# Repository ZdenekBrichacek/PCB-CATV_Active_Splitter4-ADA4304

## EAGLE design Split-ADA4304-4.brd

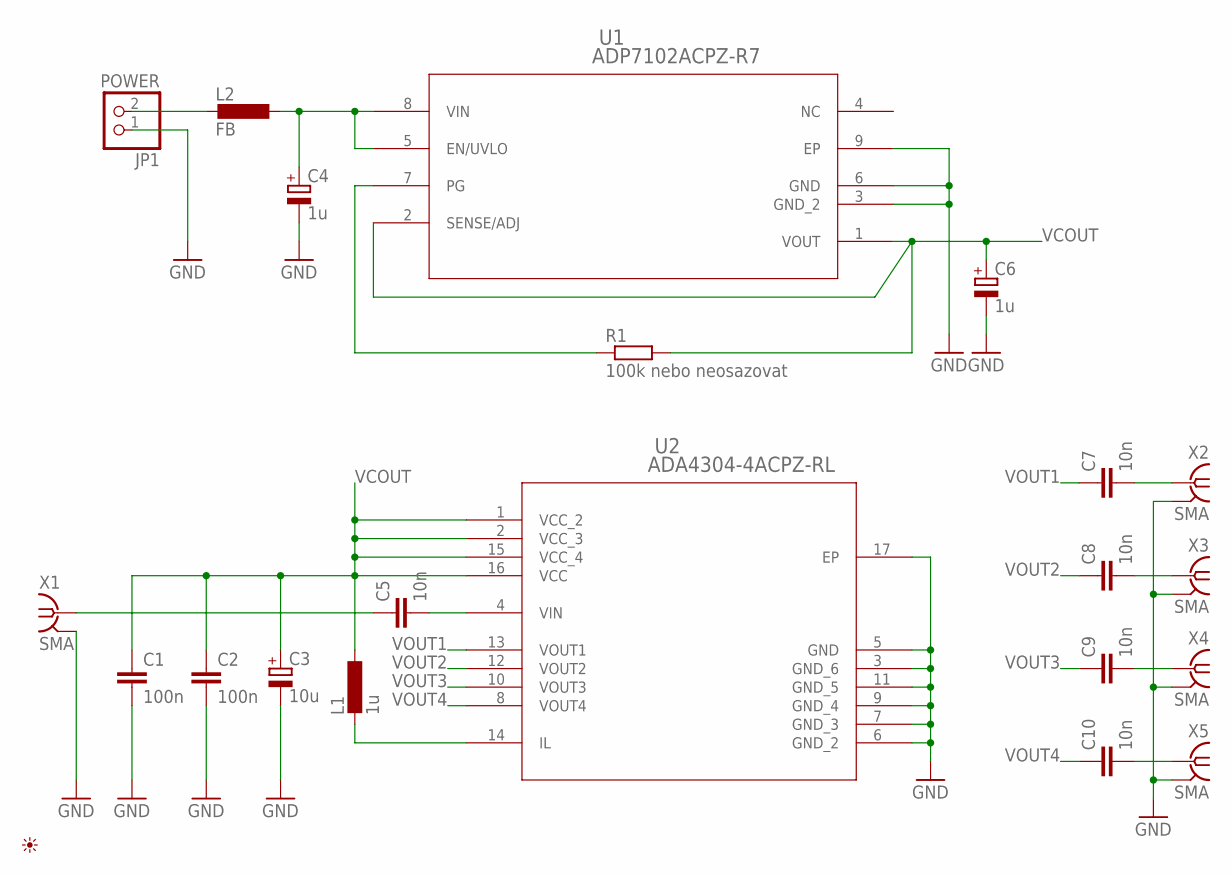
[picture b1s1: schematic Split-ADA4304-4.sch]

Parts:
C1, C2: 100n; C0603
C3: 10u; SMC_A
C4, C6: 1u; SMC_A
C5, C7, C8, C9, C10: 10n; C0603
JP1: POWER; 1X02
L1: 1u; L2012C
L2: FB; L2012C
PICTO1: PICTO_1
R1: 100k nebo neosazovat; R0603
U1: ADP7102ACPZ-R7; CP_8_5
U2: ADA4304-4ACPZ-RL; CP_16_2
X1, X2, X3, X4, X5: SMA; J502-ND-142-0701-801/806

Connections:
GND: C1.2, C2.2, C3.-, C4.-, C6.-, JP1.1, U1.3 (GND_2), U1.6 (GND), U1.9 (EP), U2.3 (GND_6), U2.5 (GND), U2.6 (GND_2), U2.7 (GND_3), U2.9 (GND_4), U2.11 (GND_5), U2.17 (EP), X1.G@1 (2), X1.G@2 (2), X1.G@3 (2), X1.G@4 (2), X2.G@1 (2), X2.G@2 (2), X2.G@3 (2), X2.G@4 (2), X3.G@1 (2), X3.G@2 (2), X3.G@3 (2), X3.G@4 (2), X4.G@1 (2), X4.G@2 (2), X4.G@3 (2), X4.G@4 (2), X5.G@1 (2), X5.G@2 (2), X5.G@3 (2), X5.G@4 (2)
unnamed: JP1.2, L2.2
unnamed: R1.1, U1.7 (PG)
unnamed: C7.2, X2.1
unnamed: C8.2, X3.1
unnamed: C9.2, X4.1
unnamed: C5.1, X1.1
unnamed: C5.2, U2.4 (VIN)
unnamed: L1.2, U2.14 (IL)
unnamed: C10.2, X5.1
VCIN: C4.+, L2.1, U1.5 (EN/UVLO), U1.8 (VIN)
VCOUT: C1.1, C2.1, C3.+, C6.+, L1.1, R1.2, U1.1 (VOUT), U1.2 (SENSE/ADJ), U2.1 (VCC_2), U2.2 (VCC_3), U2.15 (VCC_4), U2.16 (VCC)
VOUT1: C7.1, U2.13 (VOUT1)
VOUT2: C8.1, U2.12 (VOUT2)
VOUT3: C9.1, U2.10 (VOUT3)
VOUT4: C10.1, U2.8 (VOUT4)

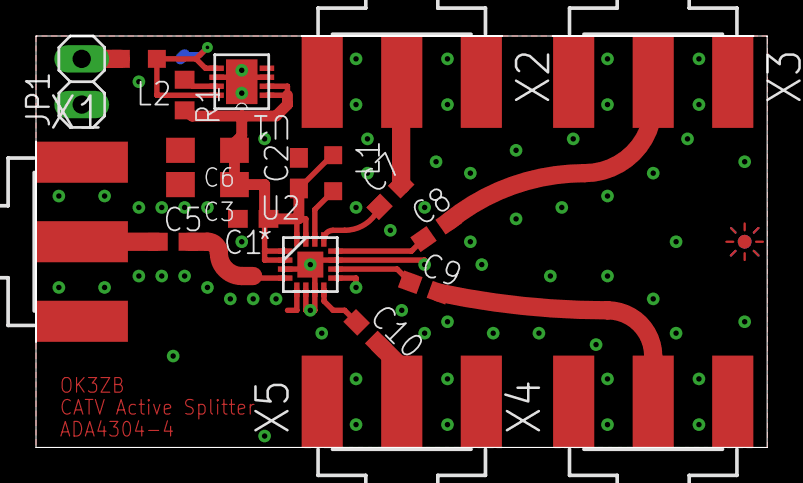
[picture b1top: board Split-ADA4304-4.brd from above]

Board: 2 copper layers, 40.6 x 22.9 mm, 22 parts (1 on the bottom side), 16 nets.

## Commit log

2017-10-10 :neckbeard: Added .gitattributes & .gitignore files
2017-10-10 Initial version
